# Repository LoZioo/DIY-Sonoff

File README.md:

# DIY-Sonoff
Simple sonoff based on the ESP-01 devboard.

# Table of contents
<!-- TOC start (generated with https://github.com/derlin/bitdowntoc) -->

- [Requirements](#requirements)
- [3D enclosure](#3d-enclosure)
- [Assembly](#assembly)
- [GPIOs mapping](#gpios-mapping)
   * [Inputs and outputs](#inputs-and-outputs)
   * [ESP8266 bootloader GPIOs configurations](#esp8266-bootloader-gpios-configurations)
   * [ESP8266 GPIOs behaviour](#esp8266-gpios-behaviour)
   * [Suggested configurations](#suggested-configurations)
- [Firmware](#firmware)
- [Circuit and PCB](#circuit-and-pcb)
- [Previews](#previews)
- [References](#references)

<!-- TOC end -->

# Requirements
To download the needed KiCad libraries, you must `cd schematics/lib` and run the [clone.sh](schematics/lib/clone.sh) script.

# 3D enclosure
The STL files for the 3D enclosure could be retrived [here](https://www.tinkercad.com/things/9bSfBo0S5Wv-diy-sonoff-enclosure).

# Assembly
- You must check the size of the `C2` capacitor before soldering it because it can be too high to be mounted under the ESP-01 module.
- The `R3` resistor must be mounted if you are going to use the `RST` pin on the `J3` header, otherwise you can place a short circuit instead.
- When you have finished mounting everything, you must map the ESP-01 GPIOs to the corresponding input and outputs.

# GPIOs mapping
You can map the four ESP-01 GPIOs by using the solder pads `JPx` on the back of the PCB. For example, if you want to use the GPIO2 as an output to control the `K2` relay, you can put a solder bridge on `JP6` between the `GPIO2` and `OUT-2` labels. This feature has been introduced in this version because of the behaviour of the GPIOs during the bootloader stage and to make the circuit fully adaptable to every possible situation.

## Inputs and outputs
On the PCB, the `IN-x` pads are shorted directly to the screw terminal `J2`, while the `OUT-x` pads are shorted to the gate pin of the corresponding `Qx` MOSFET.

## ESP8266 bootloader GPIOs configurations
When booting an ESP8266 microcontroller, the bootloader reads the following pins to establish the boot configuration:

| GPIO15 | GPIO0 | GPIO2 | Boot mode                            |
|:------:|:-----:|:-----:|--------------------------------------|
|   LOW  |  LOW  |  HIGH | Serial programming (bootloader mode) |
|   LOW  |  HIGH |  HIGH | Boot from flash                      |
|  HIGH  |  ANY  |  ANY  | Boot from SD card                    |

**Note**: On the ESP-01 dev board, the GPIO15 is not exposed and is held low by the hardware, so you can ignore the first column.

Said that, when booting the already programmed module, you must ensure that the second column configuration is selected. That's accomplished by the resistors `R1` and `R2` on the PCB.

## ESP8266 GPIOs behaviour
|  GPIO |                                 Input                                 |                                                                         Output                                                                        |        Bootloader behaviour        |                  Notes                 |
|:-----:|:---------------------------------------------------------------------:|:-----------------------------------------------------------------------------------------------------------------------------------------------------:|:----------------------------------:|:--------------------------------------:|
| GPIO0 | It must be held high during the boot phase. After, pulled up by `R1`. |                                                     Pulled up at boot by `R1`. After, it's clean.                                                     |          Pulled up by `R1`         |        Boot fails if pulled low.       |
| GPIO1 |              It must be held high during the boot phase.              | It's the UART TX pin and when booting, the bootloader sends out debug data for ~8ms. For that reason, you should not use that pin to control a relay. |    Bootloader UART debug output    | Boot fails if pulled low. UART TX pin. |
| GPIO2 | It must be held high during the boot phase. After, pulled up by `R2`. |                                                     Pulled up at boot by `R2`. After, it's clean.                                                     | High at boot and pulled up by `R2` |        Boot fails if pulled low.       |
| GPIO3 |                                 Clean                                 |                                   It's the UART RX pin. It's should be high at boot but other than that, it's clean.                                  |            High at boot            |              UART RX pin.              |

## Suggested configurations
**Smart plug**
|   \   | IN-1 | IN-2 | OUT-1 | OUT-2 |
|:-----:|:----:|:----:|:-----:|:-----:|
| GPIO0 |      |      |   X   |       |
| GPIO1 |      |      |       |       |
| GPIO2 |      |      |       |   X   |
| GPIO3 |      |      |       |       |

**Sonoff**
|   \   | IN-1 | IN-2 | OUT-1 | OUT-2 |
|:-----:|:----:|:----:|:-----:|:-----:|
| GPIO0 |      |      |   X   |       |
| GPIO1 |   X  |      |       |       |
| GPIO2 |      |      |       |   X   |
| GPIO3 |      |   X  |       |       |

# Firmware
To control the board, you can:
- Use a precompiled firmware like [Tasmota](https://tasmota.github.io/docs/) or [ESPHome](https://esphome.io/index.html).
- Build your own firmware using Arduino, ESP8266 RTOS SDK, ESP8266 NonOS SDK...

# Circuit and PCB

# Previews

# References
- [Random Nerd Tutorials: ESP8266 pinout reference](https://randomnerdtutorials.com/esp8266-pinout-reference-gpios/)
- [Tasmota](https://tasmota.github.io/docs/)
- [ESPHome](https://esphome.io/index.html)

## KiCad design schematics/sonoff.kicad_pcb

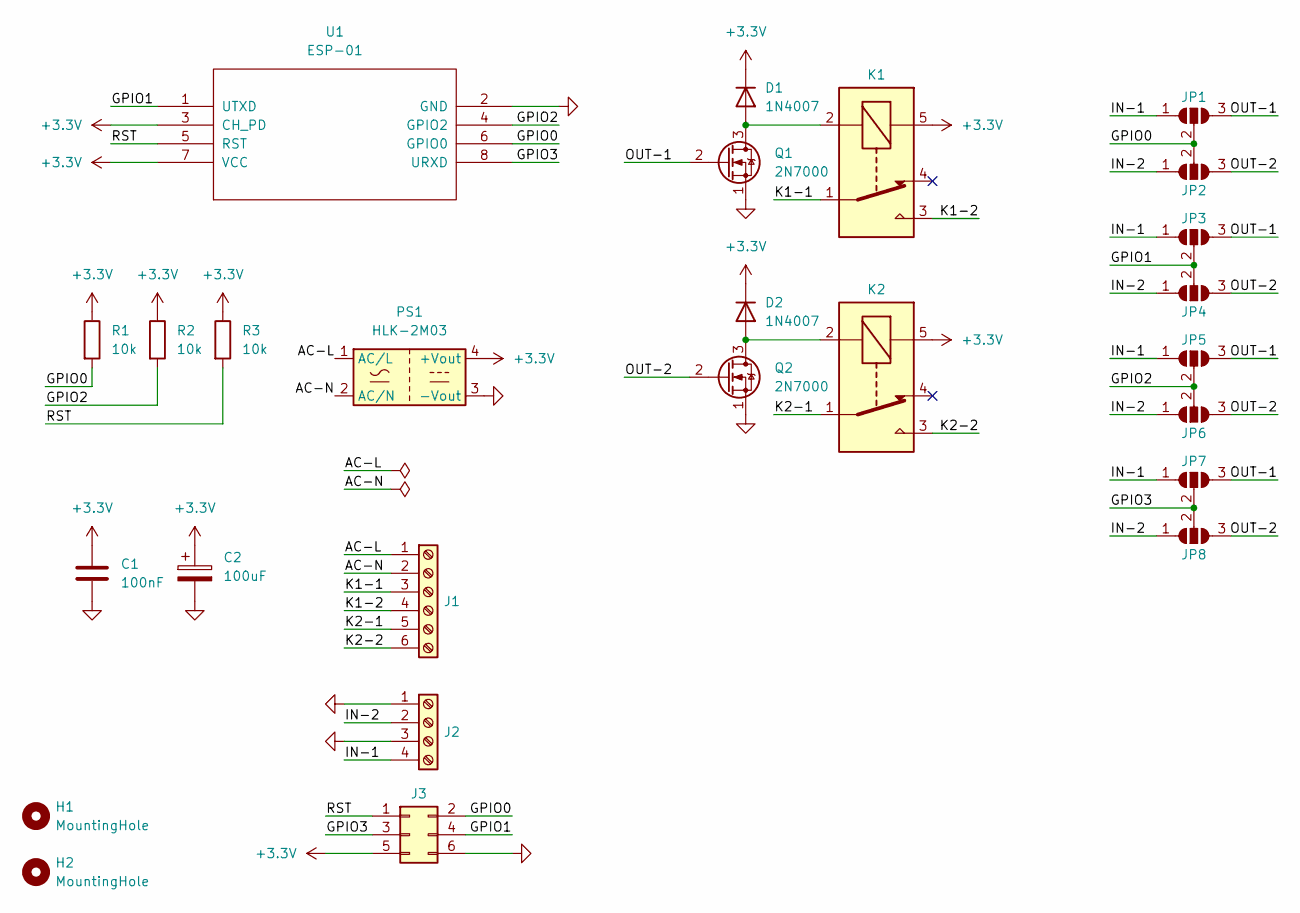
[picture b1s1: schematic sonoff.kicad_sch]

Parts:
C1: 100nF; C_Rect_L7.2mm_W2.5mm_P5.00mm_FKS2_FKP2_MKS2_MKP2
C2: 100uF; CP_Radial_D6.3mm_P2.50mm
D1, D2: 1N4007; D_DO-41_SOD81_P2.54mm_Vertical_KathodeUp
H1, H2: MountingHole; MountingHole_4.5mm_Pad_TopBottom
J1: Screw_Terminal_01x06; TerminalBlock_bornier-6_P5.08mm
J2: Screw_Terminal_01x04; TerminalBlock_4Ucon_1x04_P3.50mm_Horizontal
J3: Conn_02x03_Odd_Even; PinHeader_2x03_P2.54mm_Vertical
JP1, JP2, JP3, JP4, JP5, JP6, JP7, JP8: SolderJumper_3_Open; SolderJumper-3_P1.3mm_Open_Pad1.0x1.5mm
K1, K2: Relay_SPDT; Relay_SPDT_Omron-G5LE-1
PS1: HLK-2M03; Converter_ACDC_Hi-Link_HLK-2Mxx
Q1, Q2: 2N7000; TO-92_Inline
R1, R2, R3: 10k; R_Axial_DIN0207_L6.3mm_D2.5mm_P2.54mm_Vertical
U1: ESP-01

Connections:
+3.3V: C1.1, C2.1, D1.1 (K), D2.1 (K), J3.5, K1.5, K2.5, PS1.4 (+Vout), R1.1, R2.1, R3.1, U1.3 (CH_PD), U1.7 (VCC)
/AC-L: J1.1, PS1.1 (AC/L)
/AC-N: J1.2, PS1.2 (AC/N)
/GPIO0: J3.2, JP1.2 (C), JP2.2 (C), R1.2, U1.6 (GPIO0)
/GPIO1: J3.4, JP3.2 (C), JP4.2 (C), U1.1 (UTXD)
/GPIO2: JP5.2 (C), JP6.2 (C), R2.2, U1.4 (GPIO2)
/GPIO3: J3.3, JP7.2 (C), JP8.2 (C), U1.8 (URXD)
/IN-1: J2.4, JP1.1 (A), JP3.1 (A), JP5.1 (A), JP7.1 (A)
/IN-2: J2.2, JP2.1 (A), JP4.1 (A), JP6.1 (A), JP8.1 (A)
/K1-1: J1.3, K1.1
/K1-2: J1.4, K1.3
/K2-1: J1.5, K2.1
/K2-2: J1.6, K2.3
/OUT-1: JP1.3 (B), JP3.3 (B), JP5.3 (B), JP7.3 (B), Q1.2 (G)
/OUT-2: JP2.3 (B), JP4.3 (B), JP6.3 (B), JP8.3 (B), Q2.2 (G)
/RST: J3.1, R3.2, U1.5 (RST)
GND: C1.2, C2.2, J2.1, J2.3, J3.6, PS1.3 (-Vout), Q1.1 (S), Q2.1 (S), U1.2 (GND)
unnamed: D1.2 (A), K1.2, Q1.3 (D)
unnamed: D2.2 (A), K2.2, Q2.3 (D)

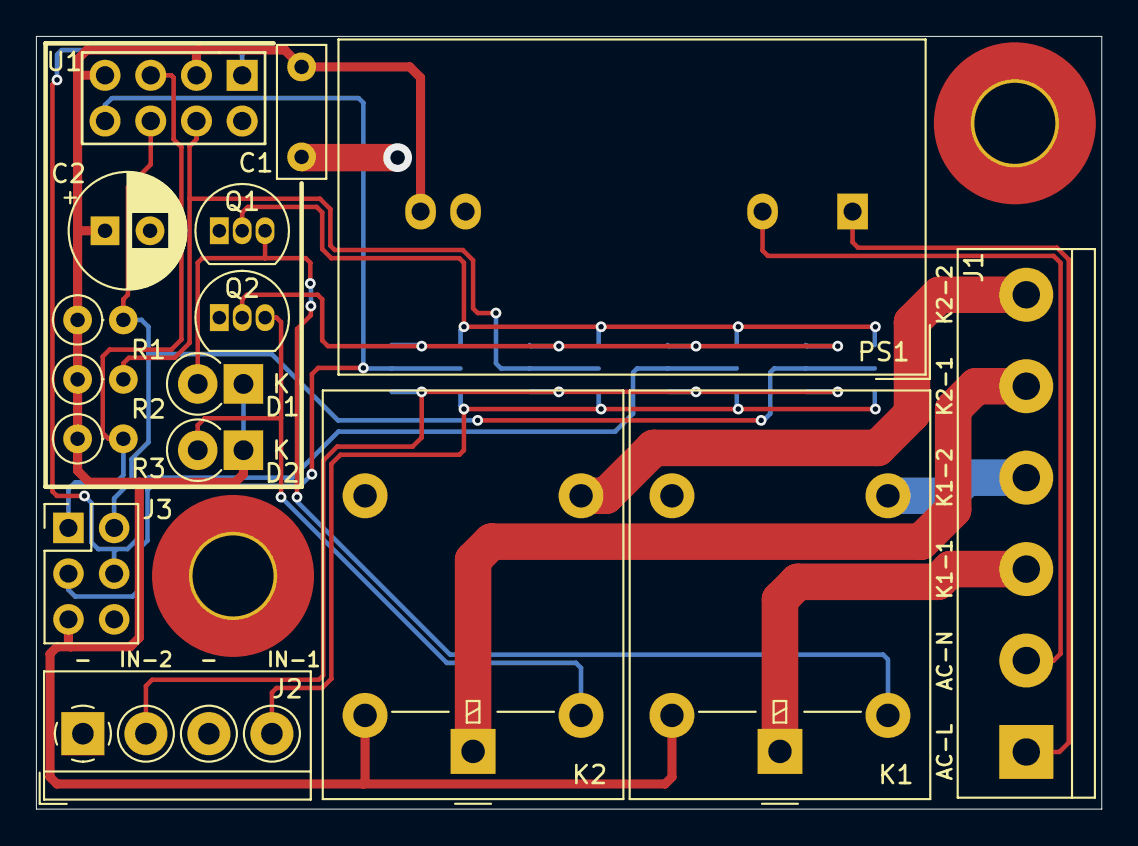
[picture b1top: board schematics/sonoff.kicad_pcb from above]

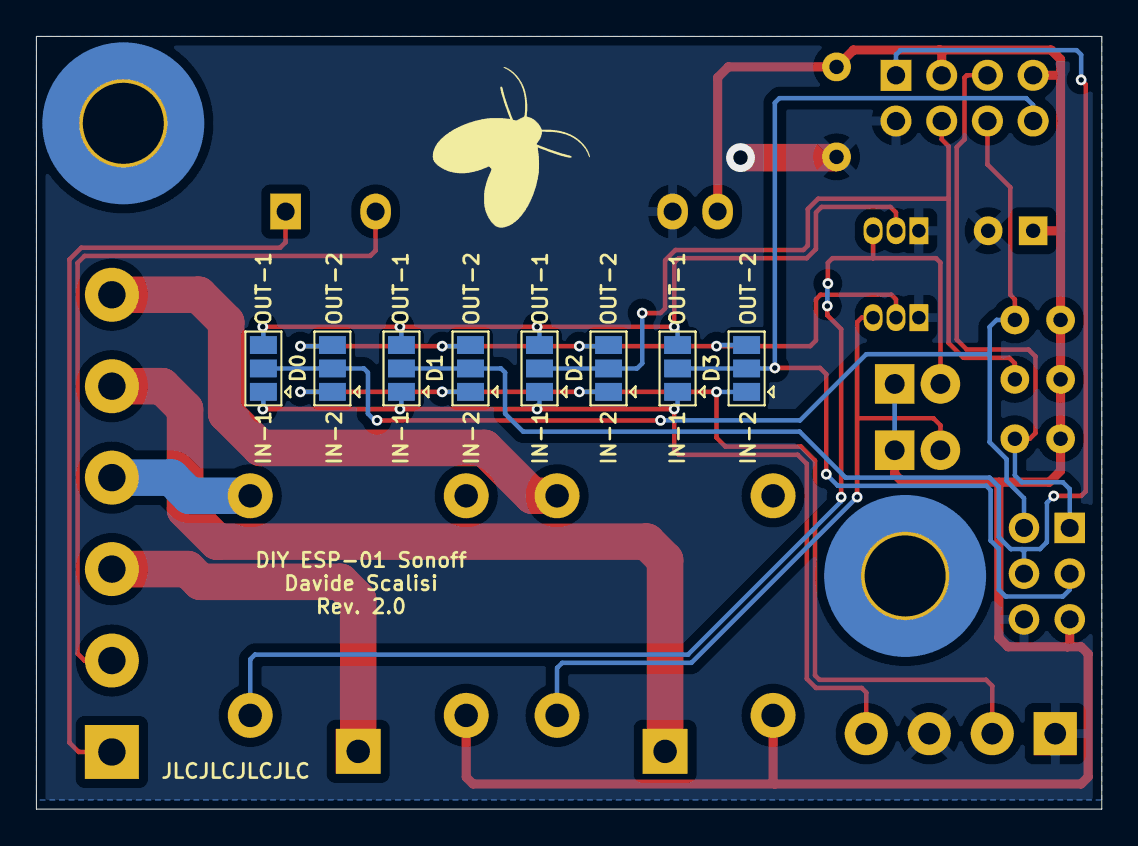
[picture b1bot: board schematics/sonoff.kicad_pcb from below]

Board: 2 copper layers, 59.2 x 42.9 mm, 26 parts (8 on the bottom side), 19 nets.

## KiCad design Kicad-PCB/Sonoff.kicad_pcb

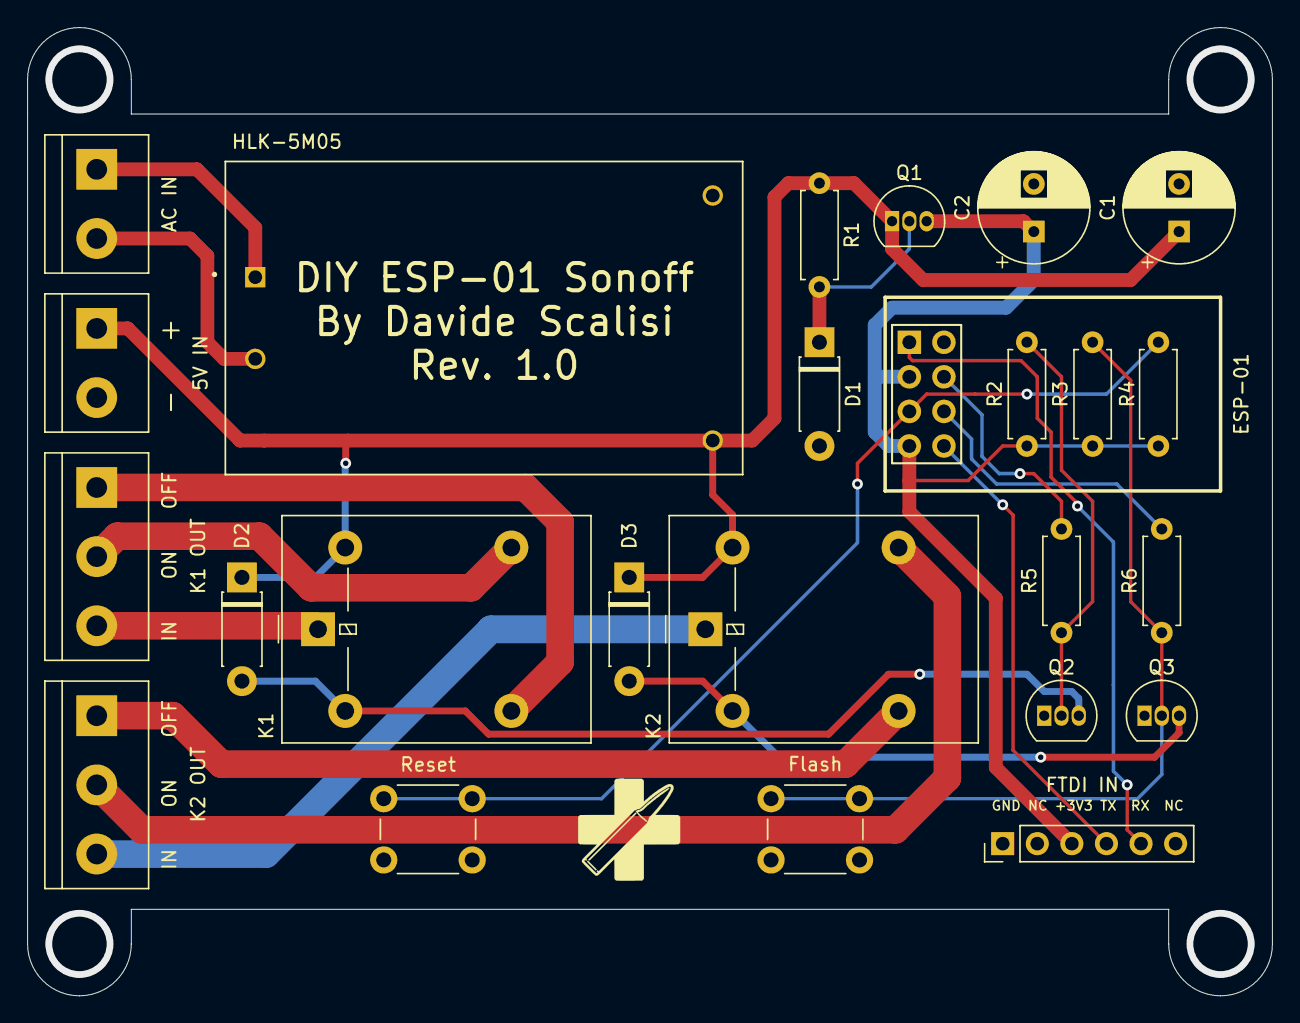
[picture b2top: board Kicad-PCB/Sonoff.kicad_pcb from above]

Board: 2 copper layers, 91.4 x 71.1 mm, 25 parts (0 on the bottom side), 21 nets.

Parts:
5V IN: 5V In; TerminalBlock_bornier-2_P5.08mm
AC IN: AC In; TerminalBlock_bornier-2_P5.08mm
C1, C2: 100u; CP_Radial_D8.0mm_P3.50mm
D1: 3.9V; D_DO-41_SOD81_P7.62mm_Horizontal
D2, D3: 1N4007; D_DO-41_SOD81_P7.62mm_Horizontal
ESP-01: ESP-01
FTDI IN: Prog; PinHeader_1x06_P2.54mm_Vertical
Flash: Flash; SW_PUSH_6mm_H5mm
HLK-5M05: HLK-5M05; CONV_HLK-5M05
K1, K2: 72mA; Relay_SPDT_Omron-G5LE-1
K1 OUT: K1 Out; TerminalBlock_bornier-3_P5.08mm
K2 OUT: K2 Out; TerminalBlock_bornier-3_P5.08mm
Q1: BC337; TO-92_Inline
Q2, Q3: 2N7000; TO-92_Inline
R1: 100; R_Axial_DIN0207_L6.3mm_D2.5mm_P7.62mm_Horizontal
R2, R3, R4: 10k; R_Axial_DIN0207_L6.3mm_D2.5mm_P7.62mm_Horizontal
R5, R6: 330; R_Axial_DIN0207_L6.3mm_D2.5mm_P7.62mm_Horizontal
Reset: Reset; SW_PUSH_6mm_H5mm

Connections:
+3V3: C2.1, ESP-01.3, ESP-01.7, FTDI IN.3, Q1.3, R2.1, R3.1, R4.2
+5V: 5V IN.1, C1.1, D2.1, D3.1, HLK-5M05.4, K1.5, K2.5, Q1.1, R1.1
GND: 5V IN.2, C1.2, C2.2, D1.2, ESP-01.2, FTDI IN.1, Flash.1, HLK-5M05.3, Q2.1, Q3.1, Reset.2
K1: Q2.2, R2.2, R5.1
K1_IN: K1.1, K1 OUT.3
K1_OFF: K1.3, K1 OUT.1
K1_ON: K1.4, K1 OUT.2
K2: Flash.2, Q3.2, R3.2, R6.1
K2_IN: K2.1, K2 OUT.3
K2_OFF: K2.3, K2 OUT.1
K2_ON: K2.4, K2 OUT.2
unnamed: D1.1, Q1.2, R1.2
unnamed: D2.2, K1.2, Q2.3
unnamed: D3.2, K2.2, Q3.3
unnamed: AC IN.1, HLK-5M05.1
unnamed: AC IN.2, HLK-5M05.2
unnamed: ESP-01.5, R4.1, Reset.1
unnamed: ESP-01.4, R5.2
unnamed: ESP-01.6, R6.2
RX: ESP-01.1, FTDI IN.5
TX: ESP-01.8, FTDI IN.4

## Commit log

2022-03-30 feat: release 1.0.0
2022-04-01 feat: added screenshots
2024-04-28 chore: repo structure
2024-04-28 feat: new PCB
2024-04-30 chore: improved design.
2024-04-30 feat
2024-05-02 feat: added clone script.
2024-05-02 !feat: first rev2 release
2024-05-02 feat: added "JLCJLCJLCJLC" to the back of the PCB.
2024-05-02 chore: added missing 3D models.
2024-05-02 docs
2024-05-17 docs: TOC and references.
